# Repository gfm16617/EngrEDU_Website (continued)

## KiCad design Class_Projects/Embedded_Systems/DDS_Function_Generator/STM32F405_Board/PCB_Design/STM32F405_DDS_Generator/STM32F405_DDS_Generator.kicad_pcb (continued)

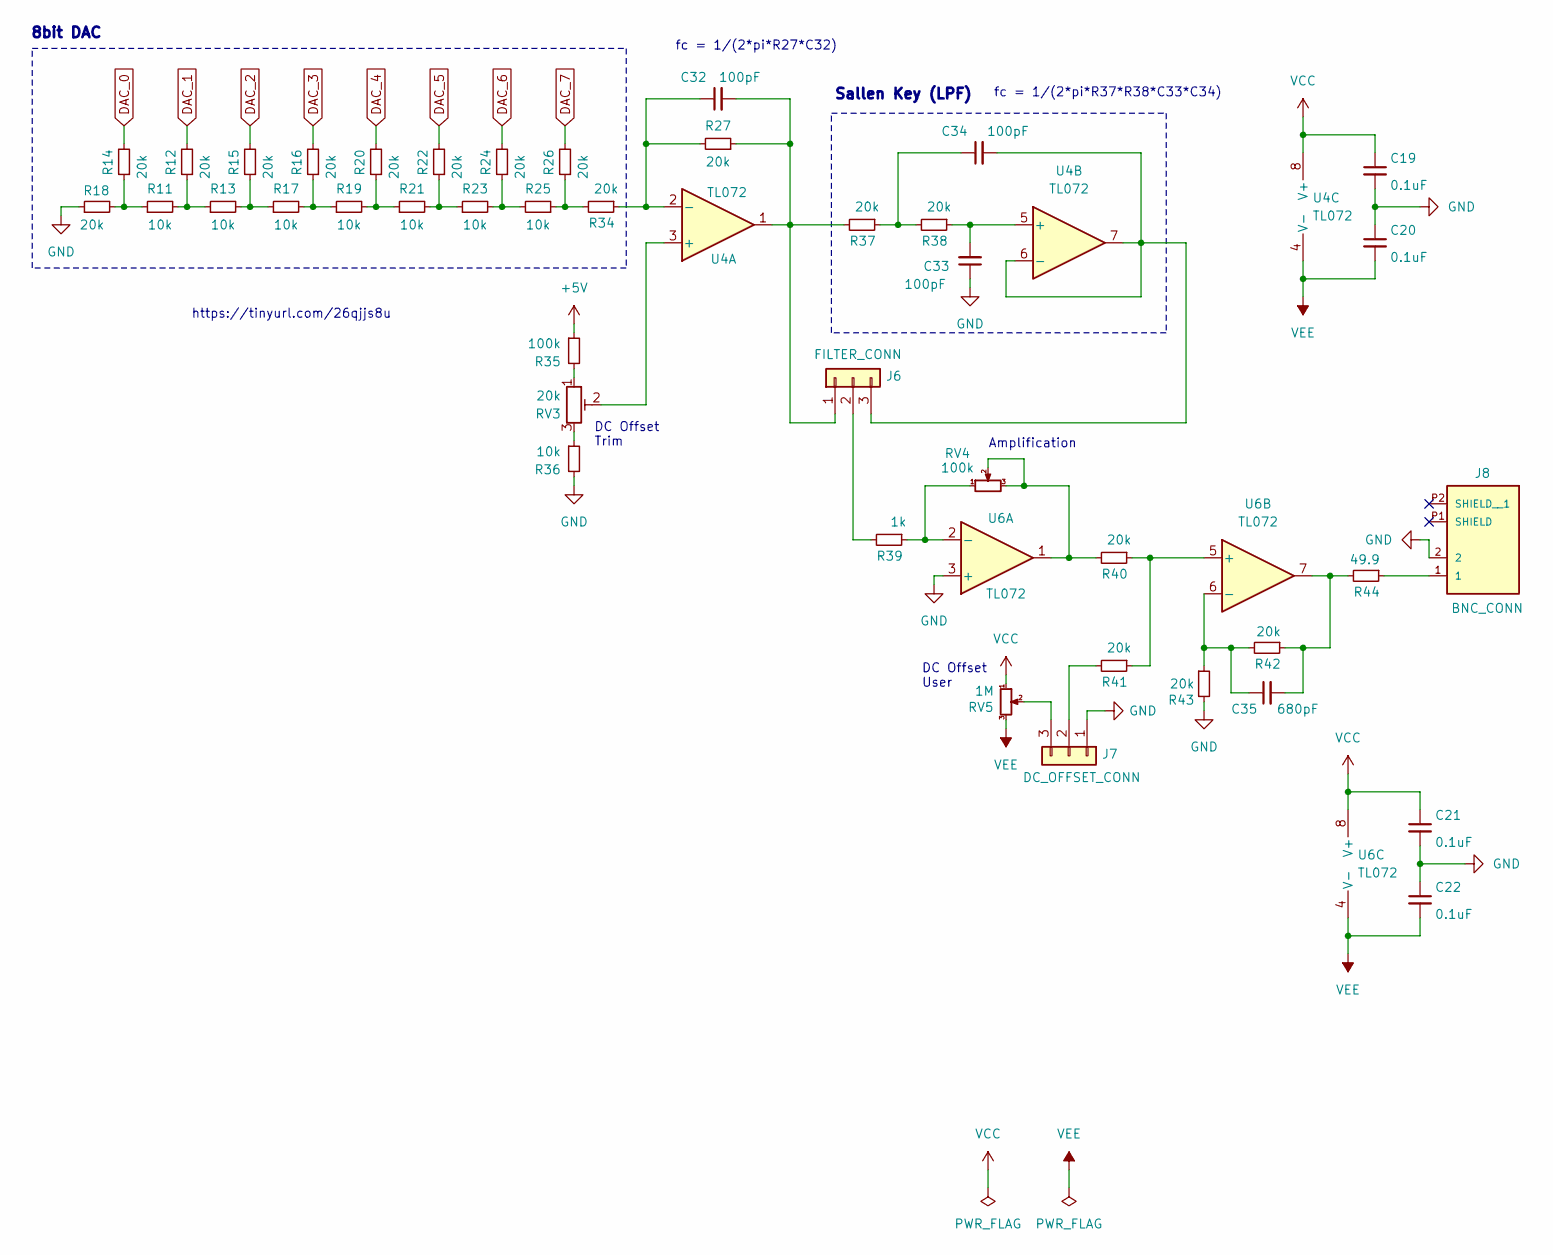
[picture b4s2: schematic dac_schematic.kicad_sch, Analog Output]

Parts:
C19, C20, C21, C22: 0.1uF; C_0805_2012Metric_Pad1.18x1.45mm_HandSolder
C32, C33, C34: 100pF; C_0805_2012Metric_Pad1.18x1.45mm_HandSolder
C35: 680pF; C_0805_2012Metric_Pad1.18x1.45mm_HandSolder
J6: FILTER_CONN; PinSocket_1x03_P2.54mm_Vertical
J7: DC_OFFSET_CONN; PinSocket_1x03_P2.54mm_Vertical
J8: BNC_CONN; BNC_RightAngle_50ohm
R11, R13, R17, R19, R21, R23, R25, R36: 10k; R_0805_2012Metric_Pad1.20x1.40mm_HandSolder
R12, R14, R15, R16, R18, R20, R22, R24, R26, R27, R34, R37, R38, R40, R41, R42, R43: 20k; R_0805_2012Metric_Pad1.20x1.40mm_HandSolder
R35: 100k; R_0805_2012Metric_Pad1.20x1.40mm_HandSolder
R39: 1k; R_0805_2012Metric_Pad1.20x1.40mm_HandSolder
R44: 49.9; R_0805_2012Metric_Pad1.20x1.40mm_HandSolder
RV3: 20k; Potentiometer_Bourns_3296W_Vertical
RV4: 100k; Potentiometer_Alps_RK09K_Single_Vertical
RV5: 1M; Potentiometer_Alps_RK09K_Single_Vertical
U4, U6: TL072; SOIC-8_3.9x4.9mm_P1.27mm

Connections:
+5V: R35.1; also elsewhere on the board
DAC_0: R14.2; also elsewhere on the board
DAC_1: R12.2; also elsewhere on the board
DAC_2: R15.2; also elsewhere on the board
DAC_3: R16.2; also elsewhere on the board
DAC_4: R20.2; also elsewhere on the board
DAC_5: R22.2; also elsewhere on the board
DAC_6: R24.2; also elsewhere on the board
DAC_7: R26.2; also elsewhere on the board
GND: C19.2, C20.1, C21.2, C22.1, C33.1, J7.1, J8.2, R18.1, R36.2, R43.2, U6.3 (+); also elsewhere on the board
unnamed: C34.1, R37.1, R38.2
unnamed: C35.2, R42.1, R44.2, U6.7
unnamed: C32.2, J6.1, R27.1, R37.2, U4.1
unnamed: J6.2, R39.2
unnamed: C34.2, J6.3, U4.6 (-), U4.7
unnamed: J7.2, R41.2
unnamed: J7.3, RV5.2
unnamed: J8.1, R44.1
unnamed: R11.1, R14.1, R18.2
unnamed: R11.2, R12.1, R13.1
unnamed: R13.2, R15.1, R17.1
unnamed: R16.1, R17.2, R19.1
unnamed: R19.2, R20.1, R21.1
unnamed: R21.2, R22.1, R23.1
unnamed: R23.2, R24.1, R25.2
unnamed: R25.1, R26.1, R34.2
unnamed: R35.2, RV3.1
unnamed: R36.1, RV3.3
unnamed: R40.2, RV4.2, RV4.3, U6.1
unnamed: RV3.2, U4.3 (+)
unnamed: C32.1, R27.2, R34.1, U4.2 (-)
unnamed: C33.2, R38.1, U4.5 (+)
unnamed: R39.1, RV4.1, U6.2 (-)
unnamed: R40.1, R41.1, U6.5 (+)
unnamed: C35.1, R42.2, R43.1, U6.6 (-)
VCC: C19.1, C21.1, RV5.1, U4.8 (V+), U6.8 (V+); also elsewhere on the board
VEE: C20.2, C22.2, RV5.3, U4.4 (V-), U6.4 (V-); also elsewhere on the board

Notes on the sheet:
8bit DAC
Sallen Key (LPF)
https://tinyurl.com/26qjjs8u
DC Offset User
fc = 1/(2*pi*R27*C32)
DC Offset Trim
fc = 1/(2*pi*R37*R38*C33*C34)
Amplification

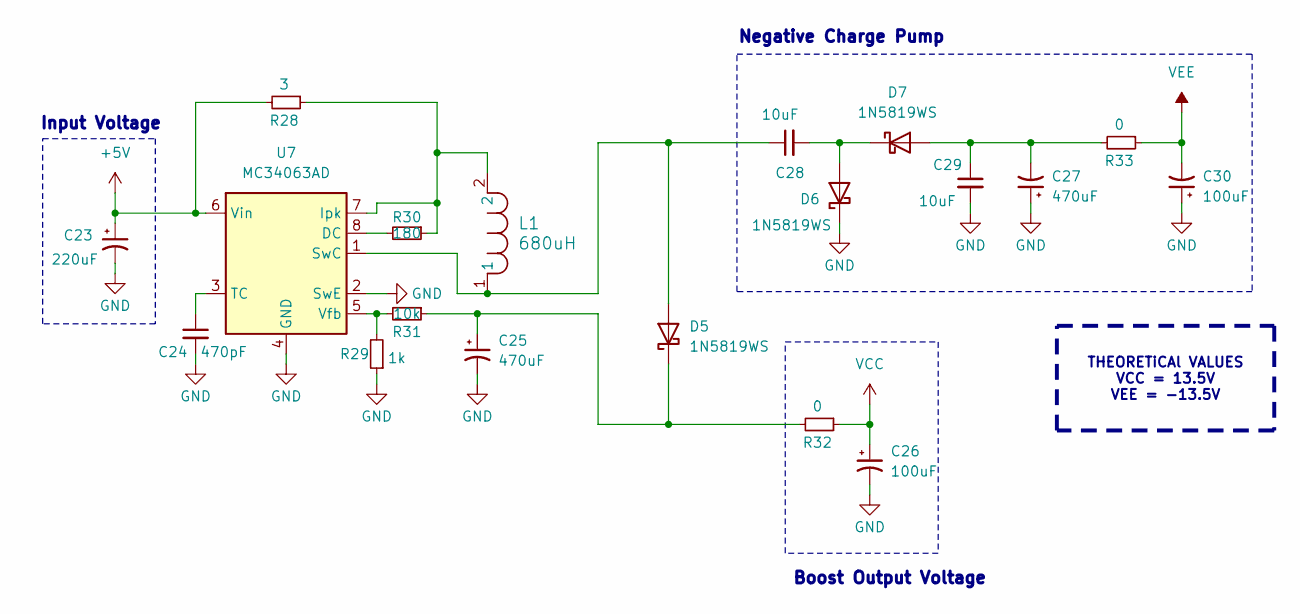
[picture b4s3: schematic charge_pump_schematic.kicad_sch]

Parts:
C23: 220uF; CAP_WCAP-ASLI_04p0X05p5_WRE
C24: 470pF; C_0805_2012Metric_Pad1.18x1.45mm_HandSolder
C25, C27: 470uF; CAP_WCAP-ASLL_08p0X10p5_WRE
C26, C30: 100uF; CAP_WCAP-ASLI_06p3X05p5_WRE
C28, C29: 10uF; C_0805_2012Metric_Pad1.18x1.45mm_HandSolder
D5, D6, D7: 1N5819WS; D_SOD-123
L1: 680uH; IND_1038-WE-TPC_WRE
R28: 3; R_0805_2012Metric_Pad1.20x1.40mm_HandSolder
R29: 1k; R_0805_2012Metric_Pad1.20x1.40mm_HandSolder
R30: 180; R_0805_2012Metric_Pad1.20x1.40mm_HandSolder
R31: 10k; R_0805_2012Metric_Pad1.20x1.40mm_HandSolder
R32, R33: 0; R_0805_2012Metric_Pad1.20x1.40mm_HandSolder
U7: MC34063AD; SOIC-8_3.9x4.9mm_P1.27mm

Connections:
+5V: C23.1, R28.2, U7.6 (Vin); also elsewhere on the board
GND: C23.2, C24.2, C25.2, C26.2, C27.1, C29.2, C30.1, D6.1 (K), R29.1, U7.2 (SwE), U7.4 (GND); also elsewhere on the board
unnamed: C28.1, D5.2 (A), L1.1, U7.1 (SwC)
unnamed: C25.1, D5.1 (K), R31.1, R32.2
unnamed: C28.2, D6.2 (A), D7.1 (K)
unnamed: C27.2, C29.1, D7.2 (A), R33.2
unnamed: R30.2, U7.8 (DC)
unnamed: L1.2, R28.1, R30.1, U7.7 (Ipk)
unnamed: C24.1, U7.3 (TC)
unnamed: R29.2, R31.2, U7.5 (Vfb)
VCC: C26.1, R32.1; also elsewhere on the board
VEE: C30.2, R33.1; also elsewhere on the board

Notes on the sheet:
THEORETiCAl VALUES VCC = 13.5V VEE = -13.5V
Negative Charge Pump
Boost Output Voltage
Input Voltage

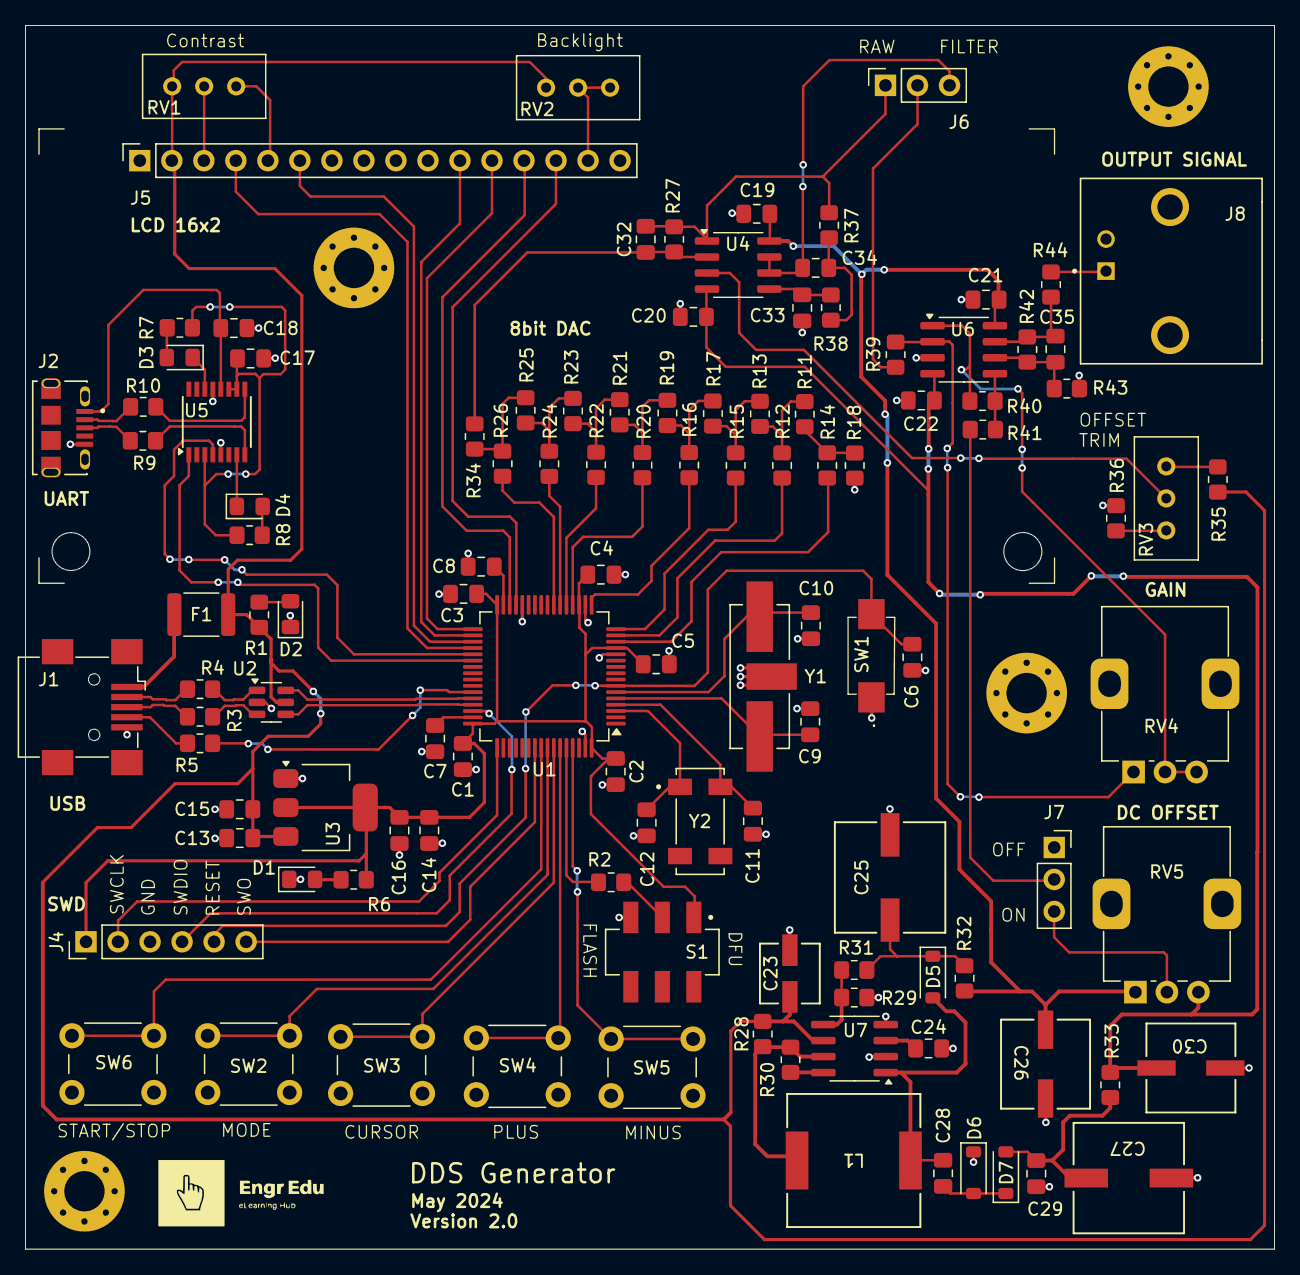
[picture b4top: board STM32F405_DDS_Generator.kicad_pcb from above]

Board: 2 copper layers, 99.1 x 97.1 mm, 119 parts (0 on the bottom side), 94 nets.

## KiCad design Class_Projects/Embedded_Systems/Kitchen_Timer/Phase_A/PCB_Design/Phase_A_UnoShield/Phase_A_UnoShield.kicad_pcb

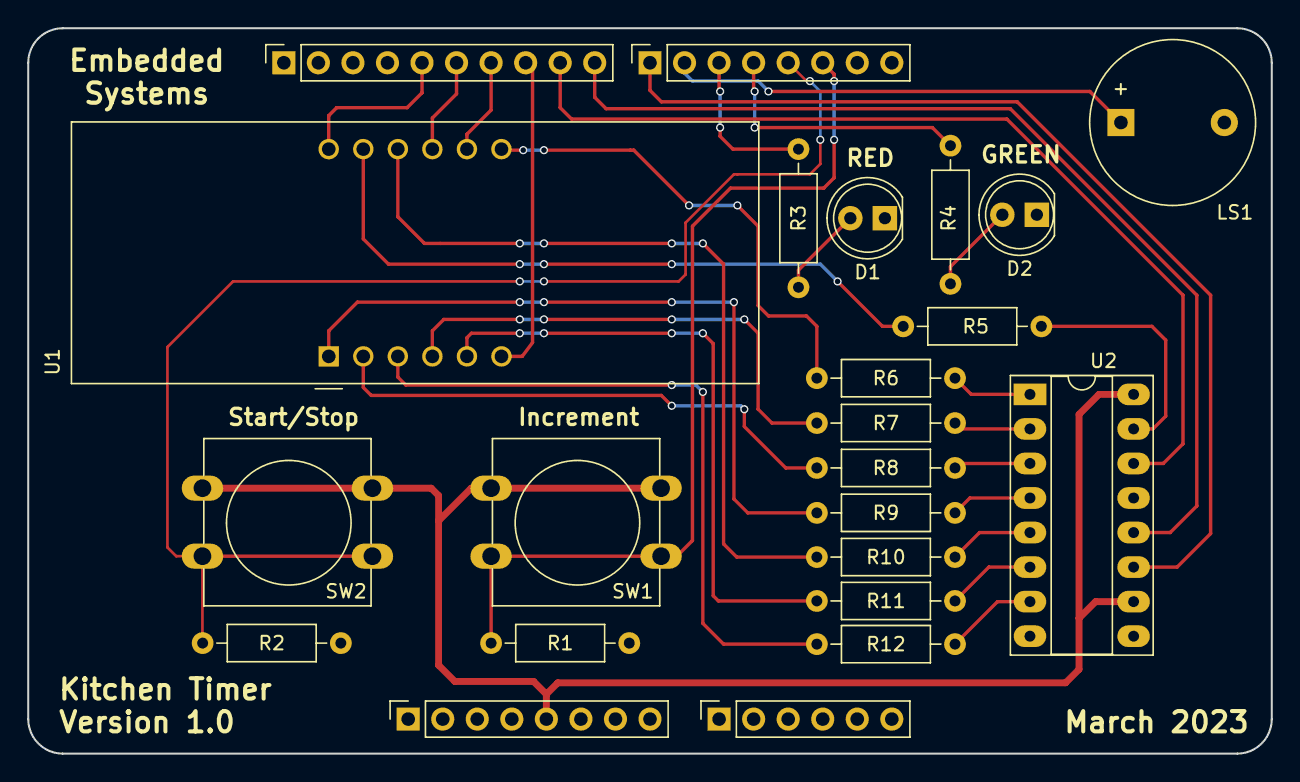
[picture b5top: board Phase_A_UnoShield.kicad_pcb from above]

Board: 2 copper layers, 91.4 x 53.3 mm, 23 parts (0 on the bottom side), 32 nets.

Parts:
D1, D2: LED; LED_D5.0mm
J1: Power; PinSocket_1x08_P2.54mm_Vertical
J2: Digital/PWM; PinSocket_1x10_P2.54mm_Vertical
J3: Analog; PinSocket_1x06_P2.54mm_Vertical
J4: Digital/PWM; PinSocket_1x08_P2.54mm_Vertical
LS1: Speaker; Buzzer_12x9.5RM7.6
R1, R2: 10k; R_Axial_DIN0207_L6.3mm_D2.5mm_P10.16mm_Horizontal
R3, R4: 330; R_Axial_DIN0207_L6.3mm_D2.5mm_P10.16mm_Horizontal
R5, R6, R7, R8, R9, R10, R11, R12: 100; R_Axial_DIN0207_L6.3mm_D2.5mm_P10.16mm_Horizontal
SW1, SW2: SW_Push; SW_PUSH-12mm
U1: CA56-12EWA
U2: 74HC595; DIP-16_W7.62mm_Socket_LongPads

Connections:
+5V: J1.5, SW1.1, SW2.1, U2.10 (~SRCLR), U2.16 (VCC)
Button_1: J4.6, R1.1, SW1.2
Button_2: J4.5, R2.1, SW2.2
Buzzer: J4.2, LS1.1
DS: J2.9, U2.14 (SER)
Dig1: J2.5, U1.12 (CA1)
Dig2: J2.6, U1.9 (CA2)
Dig3: J2.7, U1.8 (CA3)
Dig4: J2.8, U1.6 (CA4)
GND: D1.1 (K), D2.1 (K), J1.6, J1.7, J2.4, LS1.2, R1.2, R2.2, U2.8 (GND), U2.13 (~OE)
GREEN_LED: J4.4, R4.1
unnamed: D1.2 (A), R3.2
unnamed: D2.2 (A), R4.2
unnamed: R12.2, U1.3 (DPX)
unnamed: R5.2, U1.11 (a)
unnamed: R6.2, U1.7 (b)
unnamed: R7.2, U1.4 (c)
unnamed: R8.2, U1.2 (d)
unnamed: R9.2, U1.1 (e)
unnamed: R10.2, U1.10 (f)
unnamed: R11.2, U1.5 (g)
RED_LED: J4.3, R3.1
SH_CP: J4.1, U2.11 (SRCLK)
ST_CP: J2.10, U2.12 (RCLK)
a: R5.1, U2.15 (QA)
b: R6.1, U2.1 (QB)
c: R7.1, U2.2 (QC)
d: R8.1, U2.3 (QD)
dp: R12.1, U2.7 (QH)
e: R9.1, U2.4 (QE)
f: R10.1, U2.5 (QF)
g: R11.1, U2.6 (QG)

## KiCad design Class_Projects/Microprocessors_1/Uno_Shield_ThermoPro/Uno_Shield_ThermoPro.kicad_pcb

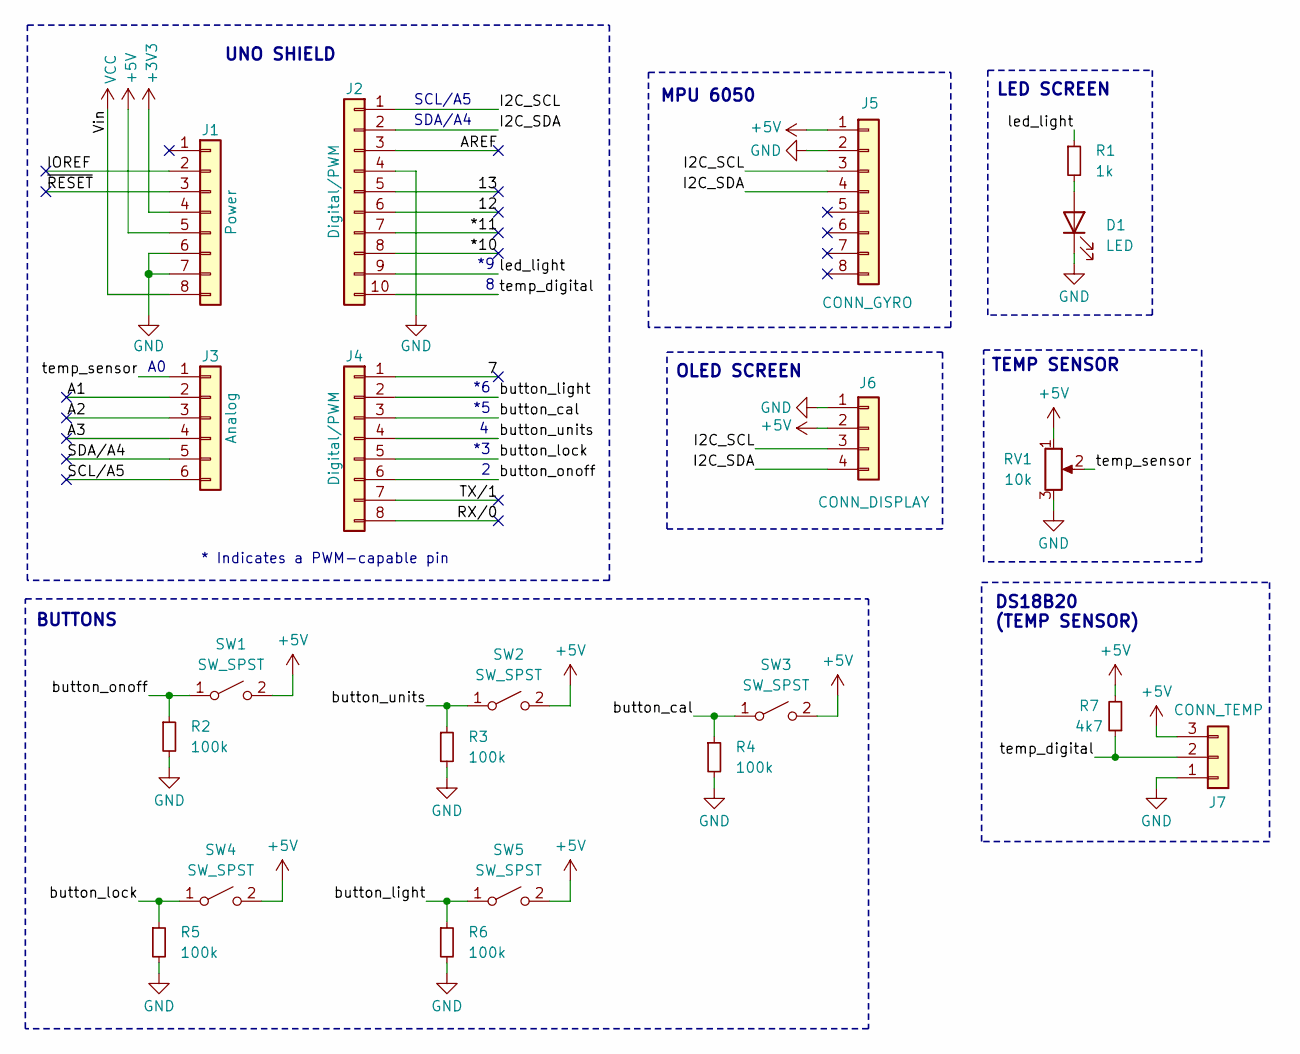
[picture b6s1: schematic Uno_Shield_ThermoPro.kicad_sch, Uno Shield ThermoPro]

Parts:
D1: LED; LED_D5.0mm
J1: Power; PinSocket_1x08_P2.54mm_Vertical
J2: Digital/PWM; PinSocket_1x10_P2.54mm_Vertical
J3: Analog; PinSocket_1x06_P2.54mm_Vertical
J4: Digital/PWM; PinSocket_1x08_P2.54mm_Vertical
J5: CONN_GYRO; PinSocket_1x08_P2.54mm_Vertical
J6: CONN_DISPLAY; PinSocket_1x04_P2.54mm_Vertical
J7: CONN_TEMP; JST_XH_B3B-XH-A_1x03_P2.50mm_Vertical
R1: 1k; R_Axial_DIN0207_L6.3mm_D2.5mm_P10.16mm_Horizontal
R2, R3, R4, R5, R6: 100k; R_Axial_DIN0207_L6.3mm_D2.5mm_P10.16mm_Horizontal
R7: 4k7; R_Axial_DIN0207_L6.3mm_D2.5mm_P10.16mm_Horizontal
RV1: 10k; Potentiometer_Bourns_3386P_Vertical
SW1, SW2, SW3, SW4, SW5: SW_SPST; SW_PUSH_6mm

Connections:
+3V3: J1.4
+5V: J1.5, J5.1, J6.2, J7.3, R7.2, RV1.1, SW1.2 (B), SW2.2 (B), SW3.2 (B), SW4.2 (B), SW5.2 (B)
/7: J4.1
/12: J2.6
/13: J2.5
/*10: J2.8
/*11: J2.7
/A1: J3.2
/A2: J3.3
/A3: J3.4
/AREF: J2.3
/I2C_SCL: J2.1, J5.3, J6.3
/I2C_SDA: J2.2, J5.4, J6.4
/IOREF: J1.2
/RX/0: J4.8
/SCL/A5: J3.6
/SDA/A4: J3.5
/TX/1: J4.7
/button_cal: J4.3, R4.1, SW3.1 (A)
/button_light: J4.2, R6.1, SW5.1 (A)
/button_lock: J4.5, R5.1, SW4.1 (A)
/button_onoff: J4.6, R2.1, SW1.1 (A)
/button_units: J4.4, R3.1, SW2.1 (A)
/led_light: J2.9, R1.1
/temp_digital: J2.10, J7.2, R7.1
/temp_sensor: J3.1, RV1.2
/~RESET: J1.3
GND: D1.1 (K), J1.6, J1.7, J2.4, J5.2, J6.1, J7.1, R2.2, R3.2, R4.2, R5.2, R6.2, RV1.3
unnamed: D1.2 (A), R1.2
VCC: J1.8

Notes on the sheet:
DS18B20 (TEMP SENSOR)
OLED SCREEN
LED SCREEN
TEMP SENSOR
UNO SHIELD
MPU 6050
SCL/A5
SDA/A4
BUTTONS
* Indicates a PWM-capable pin

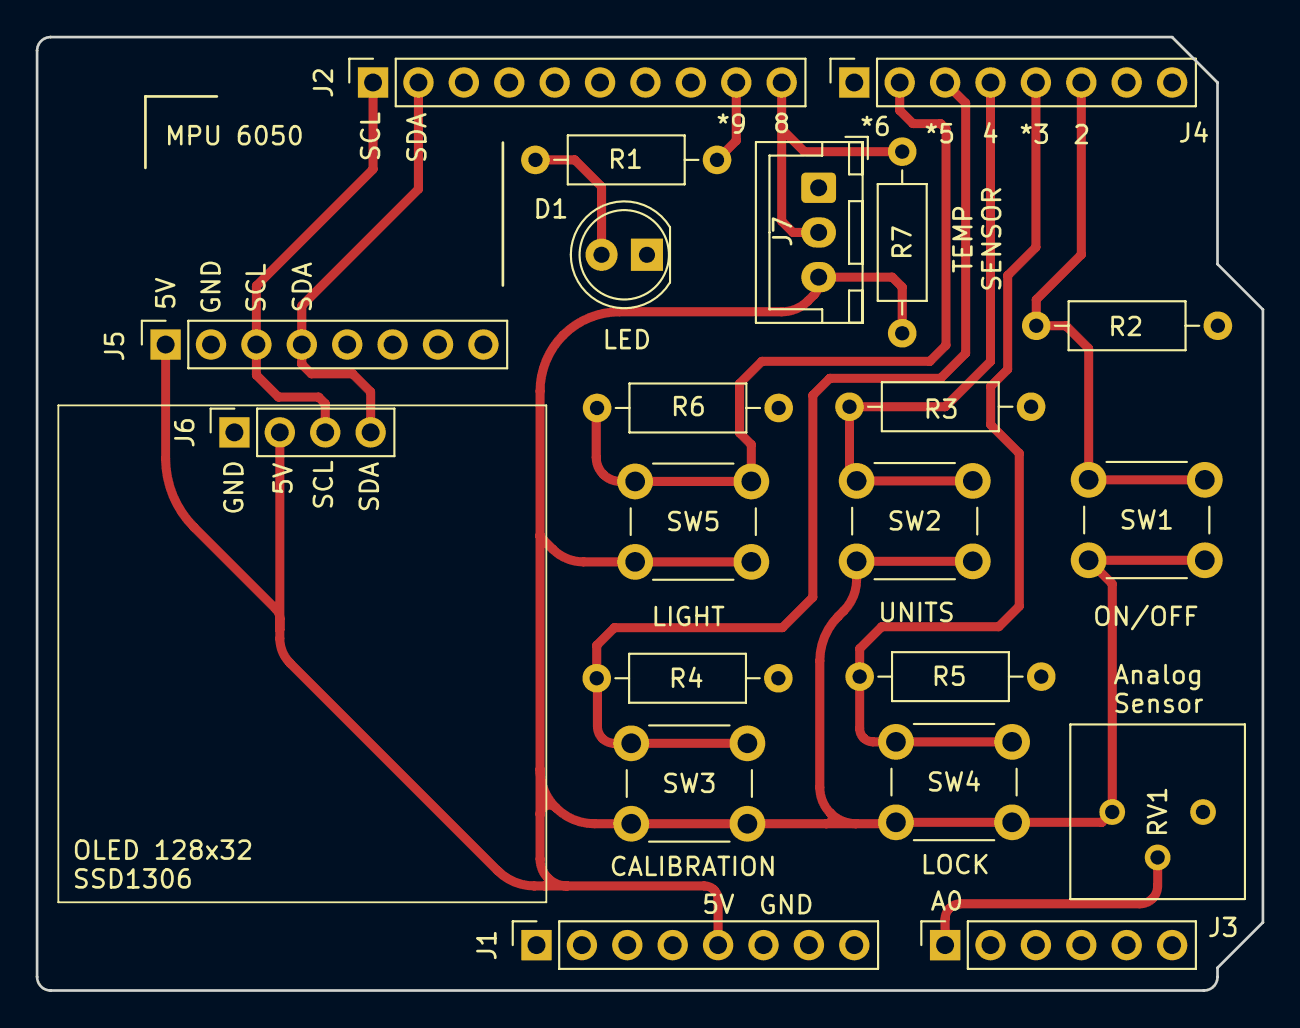
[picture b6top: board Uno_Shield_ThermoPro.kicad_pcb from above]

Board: 2 copper layers, 68.6 x 53.3 mm, 21 parts (0 on the bottom side), 13 nets.

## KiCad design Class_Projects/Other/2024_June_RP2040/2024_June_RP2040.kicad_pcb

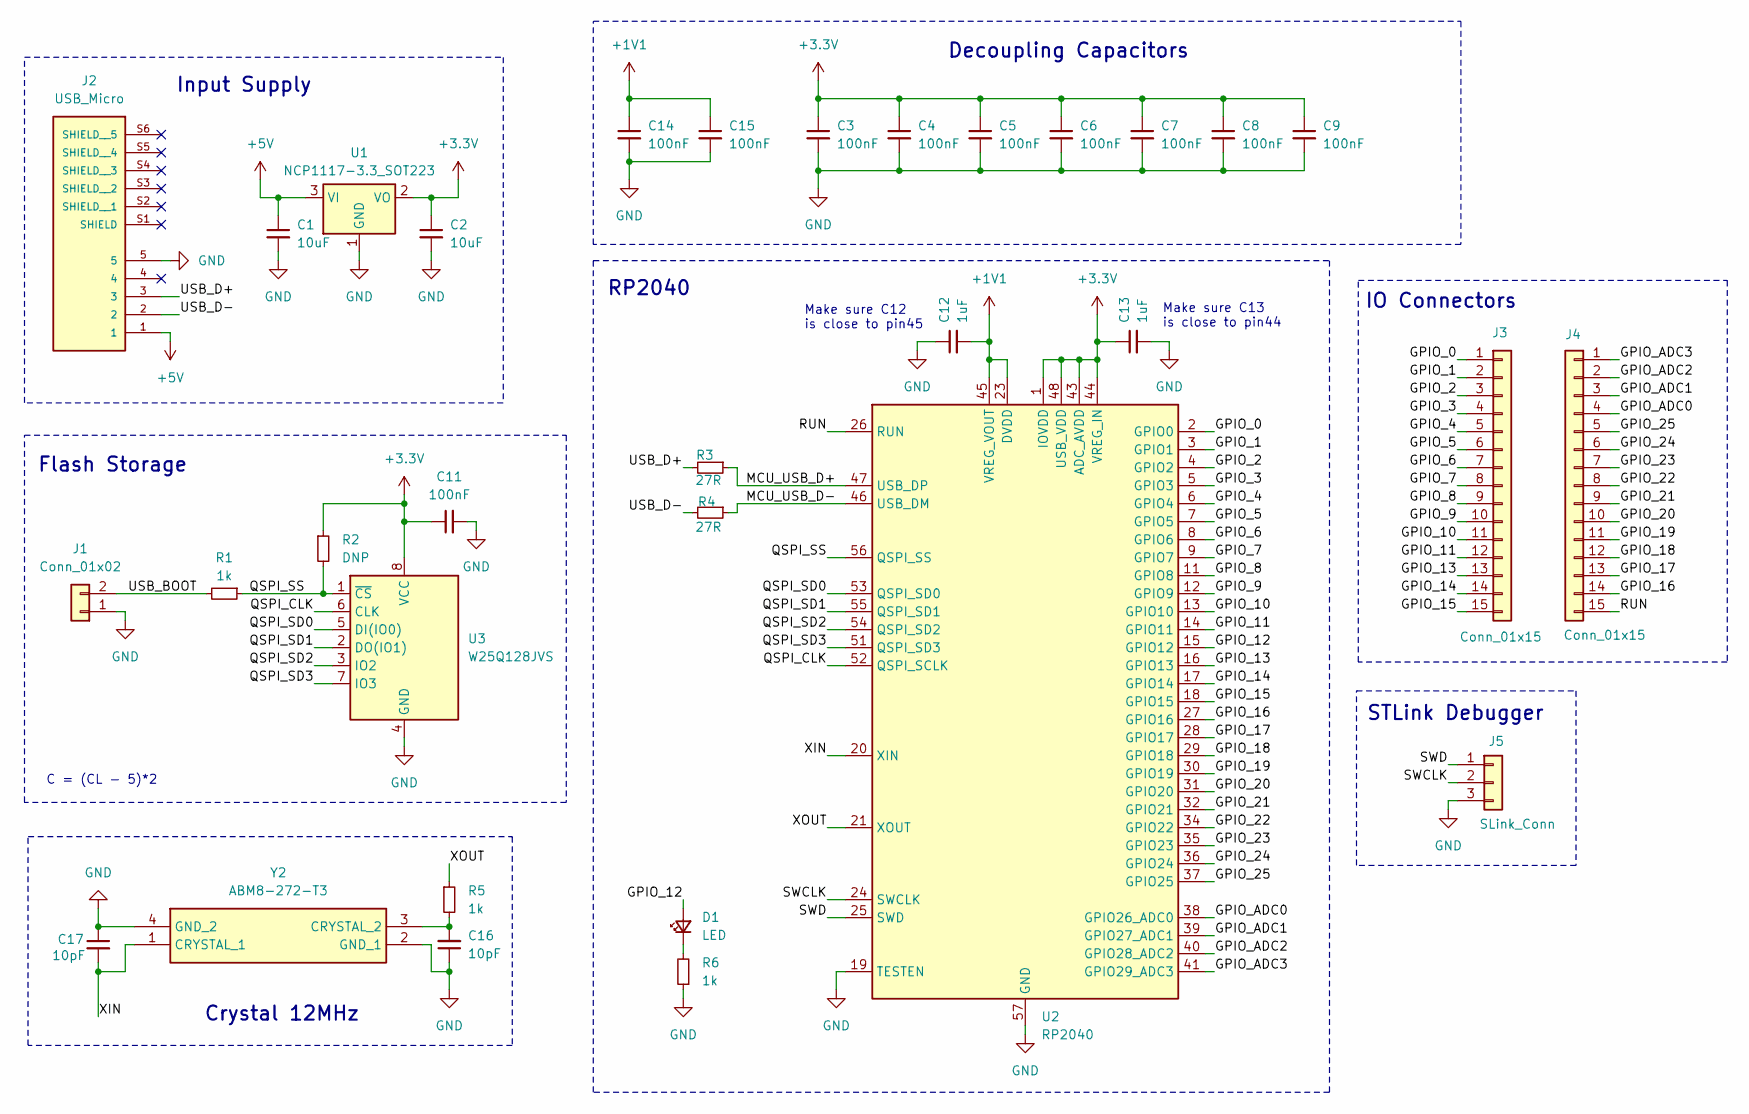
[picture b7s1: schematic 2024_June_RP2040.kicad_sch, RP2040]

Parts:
C1, C2: 10uF; C_0805_2012Metric_Pad1.18x1.45mm_HandSolder
C3, C4, C5, C6, C7, C8, C9, C11, C14, C15: 100nF; C_0402_1005Metric_Pad0.74x0.62mm_HandSolder
C12, C13: 1uF; C_0402_1005Metric_Pad0.74x0.62mm_HandSolder
C16, C17: 10pF; C_0402_1005Metric_Pad0.74x0.62mm_HandSolder
D1: LED; LED_0402_1005Metric_Pad0.77x0.64mm_HandSolder
J1: Conn_01x02; PinHeader_1x02_P2.54mm_Vertical
J2: USB_Micro; USB_B_Micro_Amphenol; PARTREV D
J3, J4: Conn_01x15; PinHeader_1x15_P2.54mm_Vertical
J5: SLink_Conn; PinHeader_1x03_P2.54mm_Vertical
R1, R5, R6: 1k; R_0402_1005Metric_Pad0.72x0.64mm_HandSolder
R2: DNP; R_0402_1005Metric_Pad0.72x0.64mm_HandSolder
R3, R4: 27R; R_0402_1005Metric_Pad0.72x0.64mm_HandSolder
U1: NCP1117-3.3_SOT223; SOT-223-3_TabPin2
U2: RP2040; QFN-56-1EP_7x7mm_P0.4mm_EP3.2x3.2mm
U3: W25Q128JVS; SOIC-8_5.23x5.23mm_P1.27mm
Y2: ABM8-272-T3; Crytal_ABM8-272-T3; Manufacturer_Part_Number ABM8-272-T3; Mouser Part Number 815-ABM8-272-T3

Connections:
+1V1: C12.2, C14.1, C15.1, U2.23 (DVDD), U2.45 (VREG_VOUT), U2.50 (DVDD)
+3.3V: C2.1, C3.1, C4.1, C5.1, C6.1, C7.1, C8.1, C9.1, C11.1, C13.1, R2.1, U1.2 (VO), U2.1 (IOVDD), U2.10 (IOVDD), U2.22 (IOVDD), U2.33 (IOVDD), U2.42 (IOVDD), U2.43 (ADC_AVDD), U2.44 (VREG_IN), U2.48 (USB_VDD), U2.49 (IOVDD), U3.8 (VCC)
+5V: C1.1, J2.1, U1.3 (VI)
/GPIO_0: J3.1, U2.2 (GPIO0)
/GPIO_1: J3.2, U2.3 (GPIO1)
/GPIO_2: J3.3, U2.4 (GPIO2)
/GPIO_3: J3.4, U2.5 (GPIO3)
/GPIO_4: J3.5, U2.6 (GPIO4)
/GPIO_5: J3.6, U2.7 (GPIO5)
/GPIO_6: J3.7, U2.8 (GPIO6)
/GPIO_7: J3.8, U2.9 (GPIO7)
/GPIO_8: J3.9, U2.11 (GPIO8)
/GPIO_9: J3.10, U2.12 (GPIO9)
/GPIO_10: J3.11, U2.13 (GPIO10)
/GPIO_11: J3.12, U2.14 (GPIO11)
/GPIO_12: D1.2 (A), U2.15 (GPIO12)
/GPIO_13: J3.13, U2.16 (GPIO13)
/GPIO_14: J3.14, U2.17 (GPIO14)
/GPIO_15: J3.15, U2.18 (GPIO15)
/GPIO_16: J4.14, U2.27 (GPIO16)
/GPIO_17: J4.13, U2.28 (GPIO17)
/GPIO_18: J4.12, U2.29 (GPIO18)
/GPIO_19: J4.11, U2.30 (GPIO19)
/GPIO_20: J4.10, U2.31 (GPIO20)
/GPIO_21: J4.9, U2.32 (GPIO21)
/GPIO_22: J4.8, U2.34 (GPIO22)
/GPIO_23: J4.7, U2.35 (GPIO23)
/GPIO_24: J4.6, U2.36 (GPIO24)
/GPIO_25: J4.5, U2.37 (GPIO25)
/GPIO_ADC0: J4.4, U2.38 (GPIO26_ADC0)
/GPIO_ADC1: J4.3, U2.39 (GPIO27_ADC1)
/GPIO_ADC2: J4.2, U2.40 (GPIO28_ADC2)
/GPIO_ADC3: J4.1, U2.41 (GPIO29_ADC3)
/MCU_USB_D+: R3.1, U2.47 (USB_DP)
/MCU_USB_D-: R4.1, U2.46 (USB_DM)
/QSPI_CLK: U2.52 (QSPI_SCLK), U3.6 (CLK)
/QSPI_SD0: U2.53 (QSPI_SD0), U3.5 (DI(IO0))
/QSPI_SD1: U2.55 (QSPI_SD1), U3.2 (DO(IO1))
/QSPI_SD2: U2.54 (QSPI_SD2), U3.3 (IO2)
/QSPI_SD3: U2.51 (QSPI_SD3), U3.7 (IO3)
/QSPI_SS: R1.1, R2.2, U2.56 (QSPI_SS), U3.1 (~CS)
/RUN: J4.15, U2.26 (RUN)
/SWCLK: J5.2, U2.24 (SWCLK)
/SWD: J5.1, U2.25 (SWD)
/USB_BOOT: J1.2, R1.2
/USB_D+: J2.3, R3.2
/USB_D-: J2.2, R4.2
/XIN: C17.2, U2.20 (XIN), Y2.1 (CRYSTAL_1)
/XOUT: R5.1, U2.21 (XOUT)
GND: C1.2, C2.2, C3.2, C4.2, C5.2, C6.2, C7.2, C8.2, C9.2, C11.2, C12.1, C13.2, C14.2, C15.2, C16.1, C17.1, J1.1, J2.5, J5.3, R6.1, U1.1 (GND), U2.19 (TESTEN), U2.57 (GND), U3.4 (GND), Y2.2 (GND_1), Y2.4 (GND_2)
unnamed: D1.1 (K), R6.2
unnamed: C16.2, R5.2, Y2.3 (CRYSTAL_2)

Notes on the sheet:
Make sure C12 is close to pin45
Crystal 12MHz
STLink Debugger
C = (CL - 5)*2
Flash Storage
IO Connectors
RP2040
Decoupling Capacitors
Input Supply
Make sure C13 is close to pin44

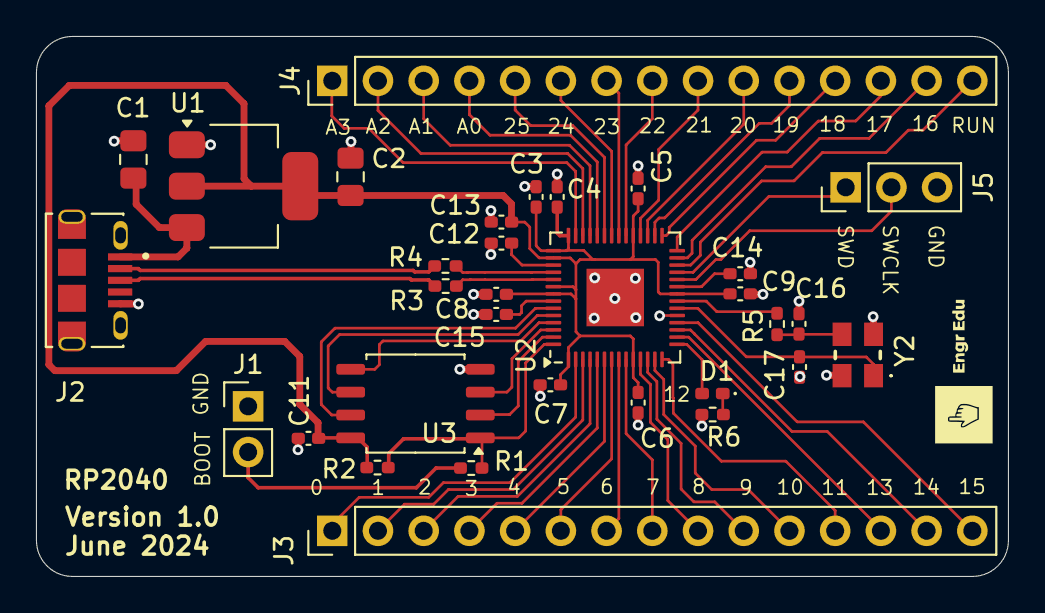
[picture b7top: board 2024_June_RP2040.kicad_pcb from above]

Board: 2 copper layers, 54.0 x 30.0 mm, 32 parts (0 on the bottom side), 52 nets.
